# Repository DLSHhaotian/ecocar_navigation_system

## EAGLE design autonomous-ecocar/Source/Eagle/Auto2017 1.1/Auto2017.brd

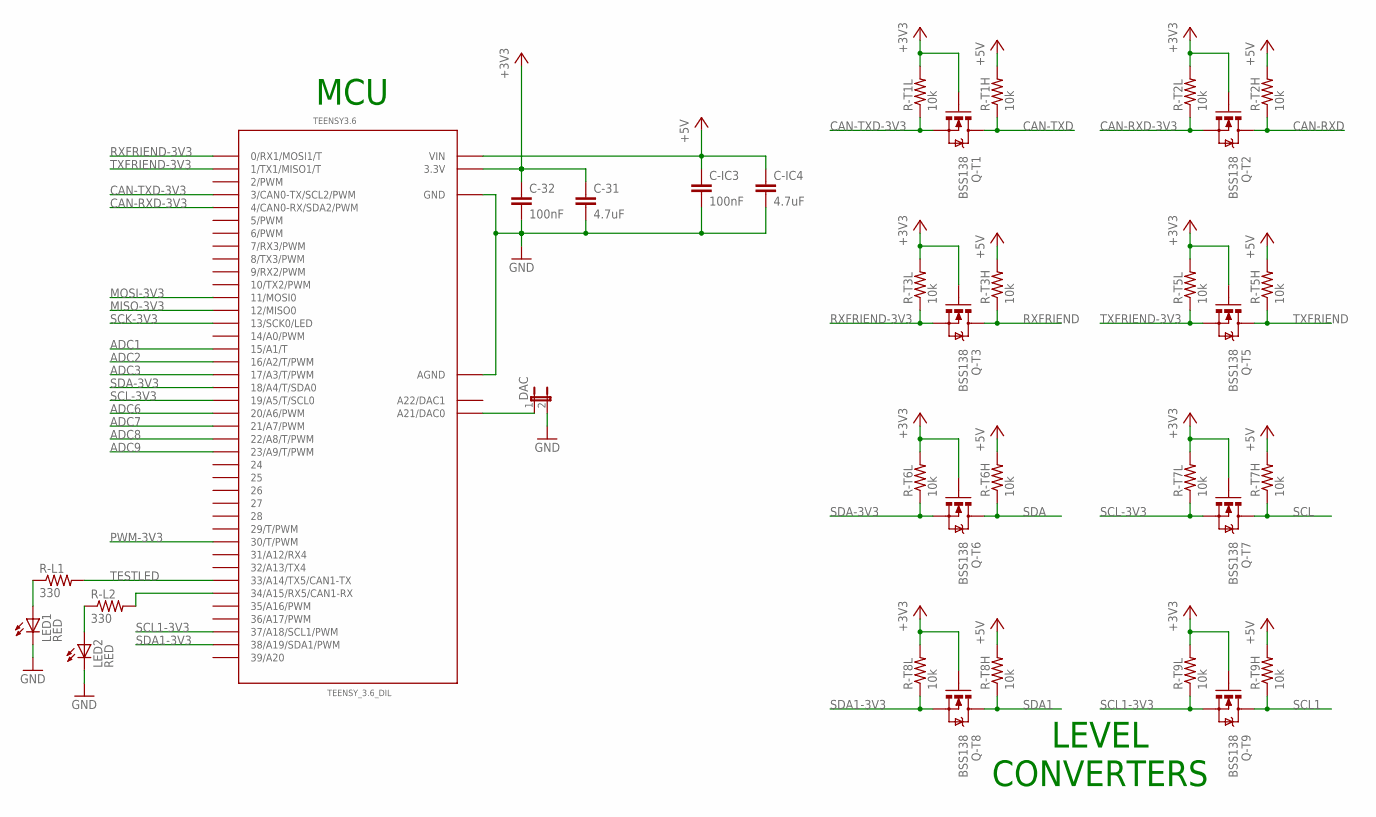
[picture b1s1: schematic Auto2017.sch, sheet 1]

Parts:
C-31: 4.7uF; 1210
C-32: 100nF; 0805
C-IC3: 100nF; 0805
C-IC4: 4.7uF; 1210
DAC: JUMPER-2PTH; 1X02
LED1, LED2: RED; LED-1206
Q-T1, Q-T2, Q-T3, Q-T5, Q-T6, Q-T7, Q-T8, Q-T9: BSS138; SOT23-3
R-L1, R-L2: 330; 0805
R-T1H, R-T1L, R-T2H, R-T2L, R-T3H, R-T3L, R-T5H, R-T5L, R-T6H, R-T6L, R-T7H, R-T7L, R-T8H, R-T8L, R-T9H, R-T9L: 10k; 0805
TEENSY3.6: TEENSY_3.6_DIL

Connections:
+3V3: C-31.1, C-32.1, Q-T1.1 (G), Q-T2.1 (G), Q-T3.1 (G), Q-T5.1 (G), Q-T6.1 (G), Q-T7.1 (G), Q-T8.1 (G), Q-T9.1 (G), R-T1L.2, R-T2L.2, R-T3L.2, R-T5L.2, R-T6L.2, R-T7L.2, R-T8L.2, R-T9L.2, TEENSY3.6.3.3V, TEENSY3.6.3.3V3 (3.3V); also elsewhere on the board
+5V: C-IC3.1, C-IC4.1, R-T1H.2, R-T2H.2, R-T3H.2, R-T5H.2, R-T6H.2, R-T7H.2, R-T8H.2, R-T9H.2, TEENSY3.6.VIN; also elsewhere on the board
ADC1: TEENSY3.6.15/A1 (15/A1/T); also elsewhere on the board
ADC2: TEENSY3.6.16/A2 (16/A2/T/PWM); also elsewhere on the board
ADC3: TEENSY3.6.17/A3 (17/A3/T/PWM); also elsewhere on the board
ADC6: TEENSY3.6.20/A6 (20/A6/PWM); also elsewhere on the board
ADC7: TEENSY3.6.21/A7 (21/A7/PWM); also elsewhere on the board
ADC8: TEENSY3.6.22/A8 (22/A8/T/PWM); also elsewhere on the board
ADC9: TEENSY3.6.23/A9 (23/A9/T/PWM); also elsewhere on the board
CAN-RXD: Q-T2.3 (D), R-T2H.1; also elsewhere on the board
CAN-RXD-3V3: Q-T2.2 (S), R-T2L.1, TEENSY3.6.4 (4/CAN0-RX/SDA2/PWM)
CAN-TXD: Q-T1.3 (D), R-T1H.1; also elsewhere on the board
CAN-TXD-3V3: Q-T1.2 (S), R-T1L.1, TEENSY3.6.3 (3/CAN0-TX/SCL2/PWM)
GND: C-31.2, C-32.2, C-IC3.2, C-IC4.2, DAC.2, LED1.C, LED2.C, TEENSY3.6.AGND, TEENSY3.6.GND, TEENSY3.6.GND1 (GND); also elsewhere on the board
MISO-3V3: TEENSY3.6.12 (12/MISO0); also elsewhere on the board
MOSI-3V3: TEENSY3.6.11 (11/MOSI0); also elsewhere on the board
unnamed: LED1.A, R-L1.1
unnamed: LED2.A, R-L2.1
unnamed: R-L2.2, TEENSY3.6.34/A15 (34/A15/RX5/CAN1-RX)
unnamed: DAC.1, TEENSY3.6.A21 (A21/DAC0)
PWM-3V3: TEENSY3.6.30 (30/T/PWM); also elsewhere on the board
RXFRIEND: Q-T3.3 (D), R-T3H.1; also elsewhere on the board
RXFRIEND-3V3: Q-T3.2 (S), R-T3L.1, TEENSY3.6.0 (0/RX1/MOSI1/T)
SCK-3V3: TEENSY3.6.13 (13/SCK0/LED); also elsewhere on the board
SCL: Q-T7.3 (D), R-T7H.1; also elsewhere on the board
SCL1: Q-T9.3 (D), R-T9H.1; also elsewhere on the board
SCL1-3V3: Q-T9.2 (S), R-T9L.1, TEENSY3.6.37/A18 (37/A18/SCL1/PWM)
SCL-3V3: Q-T7.2 (S), R-T7L.1, TEENSY3.6.19/A5 (19/A5/T/SCL0)
SDA: Q-T6.3 (D), R-T6H.1; also elsewhere on the board
SDA1: Q-T8.3 (D), R-T8H.1; also elsewhere on the board
SDA1-3V3: Q-T8.2 (S), R-T8L.1, TEENSY3.6.38/A19 (38/A19/SDA1/PWM)
SDA-3V3: Q-T6.2 (S), R-T6L.1, TEENSY3.6.18/A4 (18/A4/T/SDA0)
TESTLED: R-L1.2, TEENSY3.6.33/A14 (33/A14/TX5/CAN1-TX)
TXFRIEND: Q-T5.3 (D), R-T5H.1; also elsewhere on the board
TXFRIEND-3V3: Q-T5.2 (S), R-T5L.1, TEENSY3.6.1 (1/TX1/MISO1/T)

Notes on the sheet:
MCU
LEVEL CONVERTERS

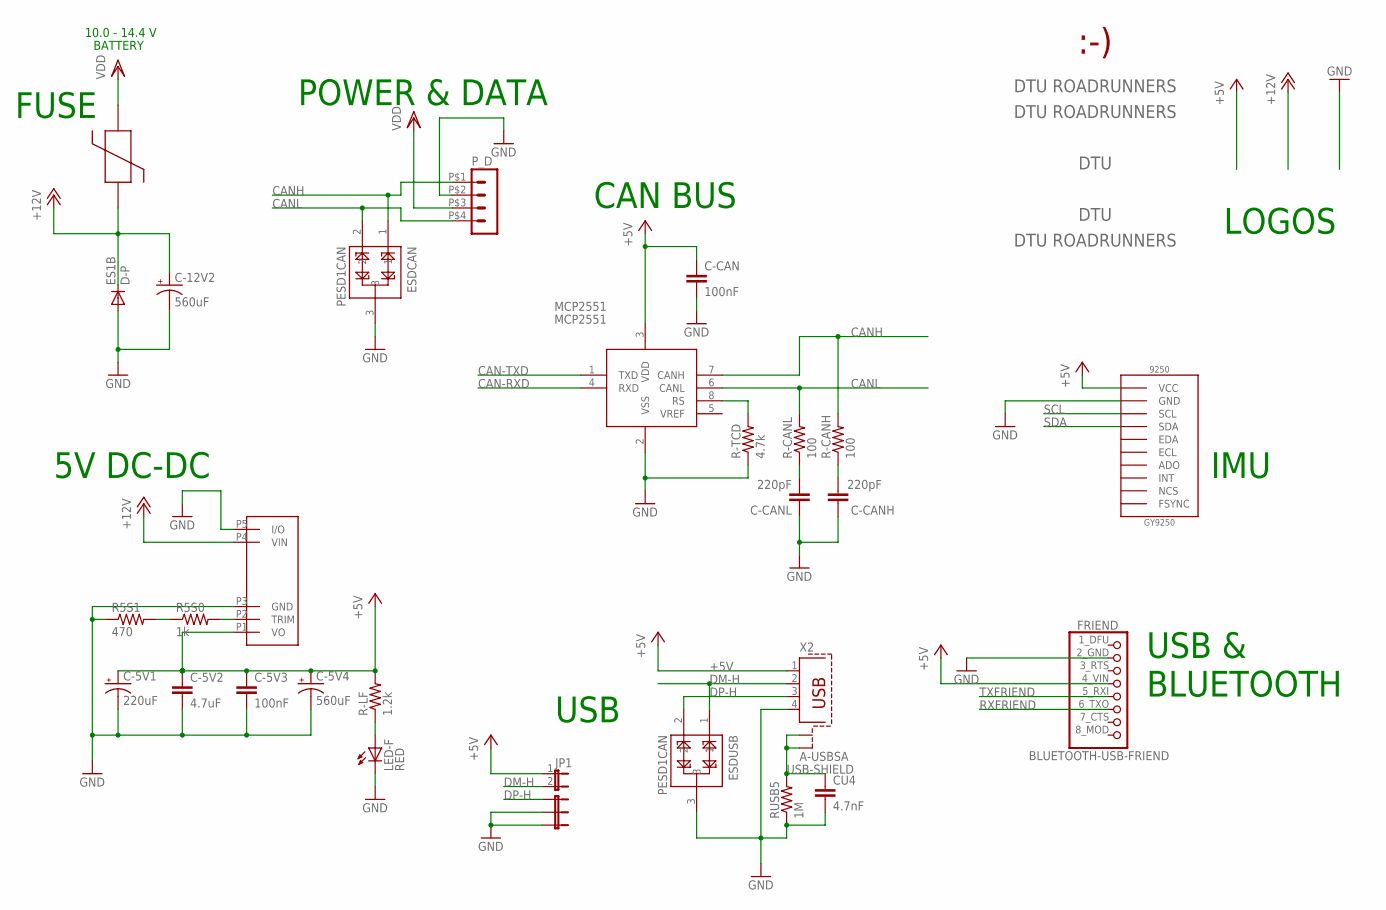
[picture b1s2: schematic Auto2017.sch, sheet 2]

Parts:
9250: GY9250
C-5V1: 220uF; PANASONIC_D
C-5V2: 4.7uF; 1210
C-5V3: 100nF; 0805
C-5V4, C-12V2: 560uF; PANASONIC_G
C-CAN: 100nF; 0805
C-CANH: 220pF; 0805
C-CANL: 220pF; 0805
CU4: 4.7nF; 0805
D-P: ES1B; SMA-DIODE
ESDCAN: PESD1CAN; SOT23-3
ESDUSB: PESD1CAN; SOT23-3
FRIEND: BLUETOOTH-USB-FRIEND; 1X08_ROUND_76
JP1: JUMPER-2PTH; 1X02
JP3: JUMPER-3PTH; 1X03
LED-F: RED; LED-1206
MAIN_FUSE: SMF_OMNI-BLOK_FUSE_BLOCK
MCP2551: MCP2551; SO-08M
P_D: HEADER_POS4_43045-0401; 43045-0400
R5S0: 1k; 0805
R5S1: 470; 0805
R-CANH: 100; 0805
R-CANL: 100; 0805
R-LF: 1.2k; 0805
R-TCD: 4.7k; 0805
RUSB5: 1M; 0805
U$1: AXA003A0XZ; SIP
U$3: DTUMEDIUM-9MM; DTU-MEDIUM-9MM
U$4, U$9: ROADRUNNERSFULL; ROADRUNNERS-FULL
U$5: ROADRUNNERSSMALL; ROADRUNNERS-SMALL
U$6: SMILEY
U$8: DTUSMALL; DTU-SMALL-5MM
X2: A-USBSA; USB-A

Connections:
+5V: 9250.P$VCC (VCC), C-5V1.+, C-5V2.1, C-5V3.1, C-5V4.+, C-CAN.1, FRIEND.4_VIN (4), JP1.1, MCP2551.3 (VDD), R-LF.2, U$1.P1 (VO), X2.1; also elsewhere on the board
+12V: C-12V2.+, D-P.C, MAIN_FUSE.PIN1, U$1.P4 (VIN)
CAN-RXD: MCP2551.4 (RXD); also elsewhere on the board
CAN-TXD: MCP2551.1 (TXD); also elsewhere on the board
CANH: ESDCAN.1, MCP2551.7 (CANH), P_D.P$1 (1), R-CANH.2
CANL: ESDCAN.2, MCP2551.6 (CANL), P_D.P$4 (4), R-CANL.2
DM-H: ESDUSB.1, JP1.2, X2.2
DP-H: ESDUSB.2, JP3.1, X2.3
GND: 9250.P$GND (GND), C-5V1.-, C-5V2.2, C-5V3.2, C-5V4.-, C-12V2.-, C-CAN.2, C-CANH.1, C-CANL.1, CU4.2, D-P.A, ESDCAN.3, ESDUSB.3, FRIEND.2_GND (2), JP3.2, JP3.3, LED-F.C, MCP2551.2 (VSS), P_D.P$2 (2), R5S1.1, R-TCD.1, RUSB5.1, U$1.P3 (GND), U$1.P5 (I/O), X2.4; also elsewhere on the board
unnamed: R5S0.1, R5S1.2
unnamed: R5S0.2, U$1.P2 (TRIM)
unnamed: LED-F.A, R-LF.1
unnamed: C-CANL.2, R-CANL.1
unnamed: C-CANH.2, R-CANH.1
RS: MCP2551.8 (RS), R-TCD.2
RXFRIEND: FRIEND.6_TXO (6); also elsewhere on the board
SCL: 9250.P$SCL (SCL); also elsewhere on the board
SDA: 9250.P$SDA (SDA); also elsewhere on the board
TXFRIEND: FRIEND.5_RXI (5); also elsewhere on the board
USB-SHIELD: CU4.1, RUSB5.2, X2.S1, X2.S2
VDD: MAIN_FUSE.PIN2, P_D.P$3 (3)

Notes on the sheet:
CAN BUS
5V DC-DC
BATTERY
10.0 - 14.4 V
POWER & DATA
FUSE
USB
USB & BLUETOOTH
IMU
LOGOS

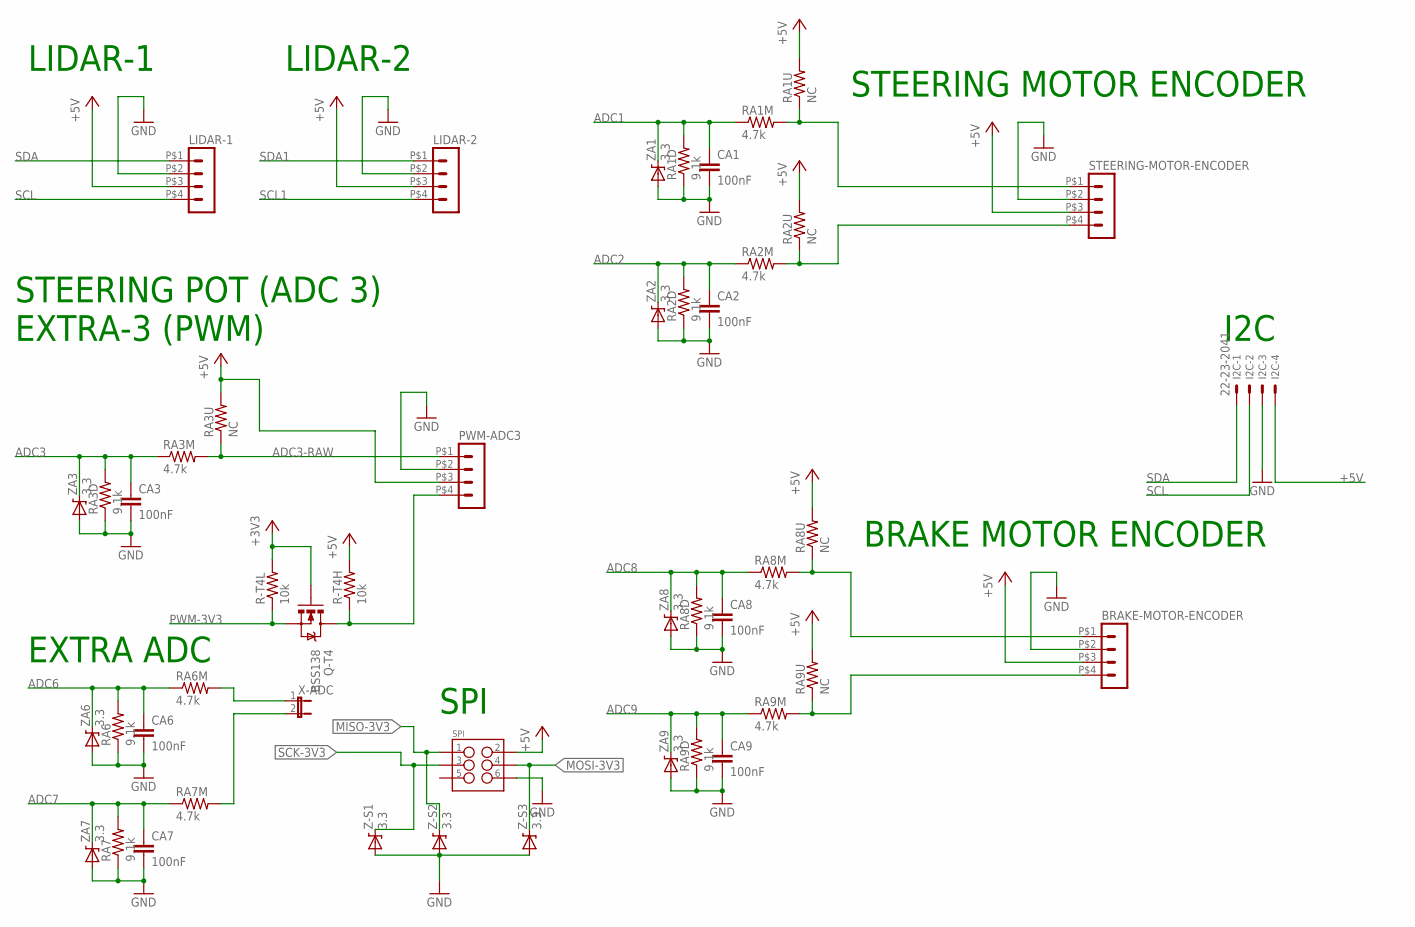
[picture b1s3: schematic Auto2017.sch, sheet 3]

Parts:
BRAKE-MOTOR-ENCODER: HEADER_POS4_43045-0401; 43045-0400
CA1, CA2, CA3, CA6, CA7, CA8, CA9: 100nF; 0805
I2C: 22-23-2041
LIDAR-1, LIDAR-2: HEADER_POS4_43045-0401; 43045-0400
PWM-ADC3: HEADER_POS4_43045-0401; 43045-0400
Q-T4: BSS138; SOT23-3
R-T4H, R-T4L: 10k; 0805
RA1D, RA2D, RA3D, RA6, RA7, RA8D, RA9D: 9.1k; 0805
RA1M, RA2M, RA3M, RA6M, RA7M, RA8M, RA9M: 4.7k; 0805
RA1U, RA2U, RA3U, RA8U, RA9U: NC; 0805
SPI: M03X2POGO_PINS; 2X3_POGO
STEERING-MOTOR-ENCODER: HEADER_POS4_43045-0401; 43045-0400
X-ADC: JUMPER-2PTH; 1X02
Z-S1, Z-S2, Z-S3: 3.3; SOD123
ZA1, ZA2, ZA3, ZA6, ZA7, ZA8, ZA9: 3.3; SOD123

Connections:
+3V3: Q-T4.1 (G), R-T4L.2; also elsewhere on the board
+5V: BRAKE-MOTOR-ENCODER.P$3 (3), I2C.4, LIDAR-1.P$3 (3), LIDAR-2.P$3 (3), PWM-ADC3.P$3 (3), R-T4H.2, RA1U.2, RA2U.2, RA3U.2, RA8U.2, RA9U.2, SPI.P$2 (2), STEERING-MOTOR-ENCODER.P$3 (3); also elsewhere on the board
ADC1: CA1.1, RA1D.2, RA1M.1, ZA1.C; also elsewhere on the board
ADC1-RAW: RA1M.2, RA1U.1, STEERING-MOTOR-ENCODER.P$1 (1)
ADC2: CA2.1, RA2D.2, RA2M.1, ZA2.C; also elsewhere on the board
ADC2-RAW: RA2M.2, RA2U.1, STEERING-MOTOR-ENCODER.P$4 (4)
ADC3: CA3.1, RA3D.2, RA3M.1, ZA3.C; also elsewhere on the board
ADC3-RAW: PWM-ADC3.P$1 (1), RA3M.2, RA3U.1
ADC6: CA6.1, RA6.2, RA6M.1, ZA6.C; also elsewhere on the board
ADC6-RAW: RA6M.2, X-ADC.1
ADC7: CA7.1, RA7.2, RA7M.1, ZA7.C; also elsewhere on the board
ADC7-RAW: RA7M.2, X-ADC.2
ADC8: CA8.1, RA8D.2, RA8M.1, ZA8.C; also elsewhere on the board
ADC8-RAW: BRAKE-MOTOR-ENCODER.P$1 (1), RA8M.2, RA8U.1
ADC9: CA9.1, RA9D.2, RA9M.1, ZA9.C; also elsewhere on the board
ADC9-RAW: BRAKE-MOTOR-ENCODER.P$4 (4), RA9M.2, RA9U.1
GND: BRAKE-MOTOR-ENCODER.P$2 (2), CA1.2, CA2.2, CA3.2, CA6.2, CA7.2, CA8.2, CA9.2, I2C.3, LIDAR-1.P$2 (2), LIDAR-2.P$2 (2), PWM-ADC3.P$2 (2), RA1D.1, RA2D.1, RA3D.1, RA6.1, RA7.1, RA8D.1, RA9D.1, SPI.P$6 (6), STEERING-MOTOR-ENCODER.P$2 (2), Z-S1.A, Z-S2.A, Z-S3.A, ZA1.A, ZA2.A, ZA3.A, ZA6.A, ZA7.A, ZA8.A, ZA9.A; also elsewhere on the board
MISO-3V3: SPI.P$1 (1), Z-S2.C; also elsewhere on the board
MOSI-3V3: SPI.P$4 (4), Z-S3.C; also elsewhere on the board
PWM-3V3: Q-T4.2 (S), R-T4L.1; also elsewhere on the board
PWM-5V: PWM-ADC3.P$4 (4), Q-T4.3 (D), R-T4H.1
SCK-3V3: SPI.P$3 (3), Z-S1.C; also elsewhere on the board
SCL: I2C.2, LIDAR-1.P$4 (4); also elsewhere on the board
SCL1: LIDAR-2.P$4 (4); also elsewhere on the board
SDA: I2C.1, LIDAR-1.P$1 (1); also elsewhere on the board
SDA1: LIDAR-2.P$1 (1); also elsewhere on the board

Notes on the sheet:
STEERING POT (ADC 3) EXTRA-3 (PWM)
SPI
LIDAR-1
LIDAR-2
STEERING MOTOR ENCODER
I2C
BRAKE MOTOR ENCODER
EXTRA ADC

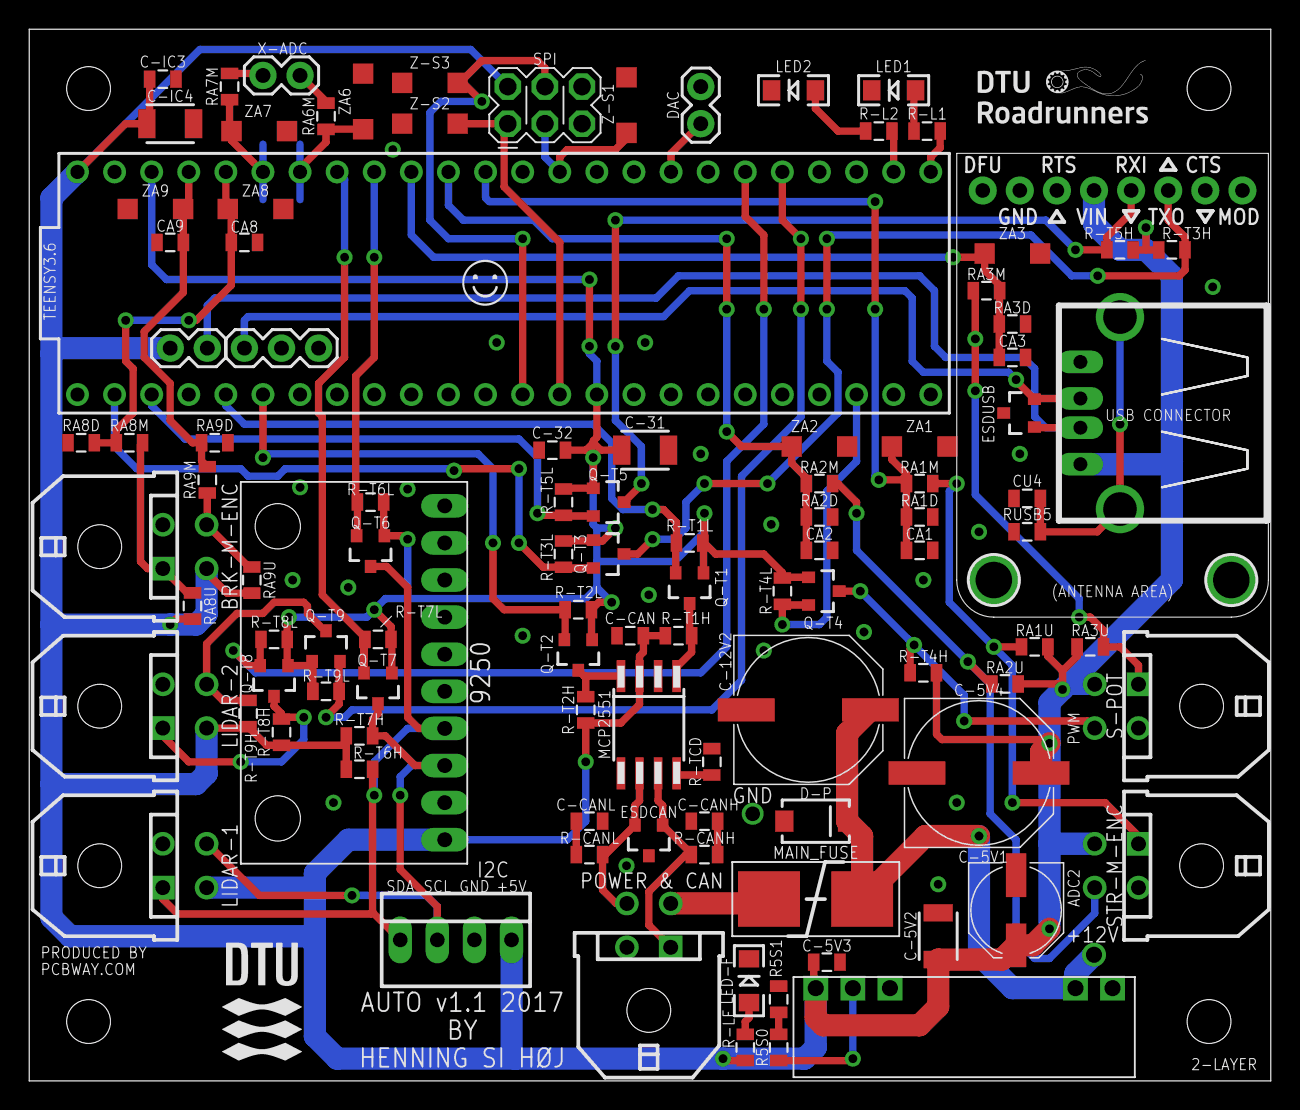
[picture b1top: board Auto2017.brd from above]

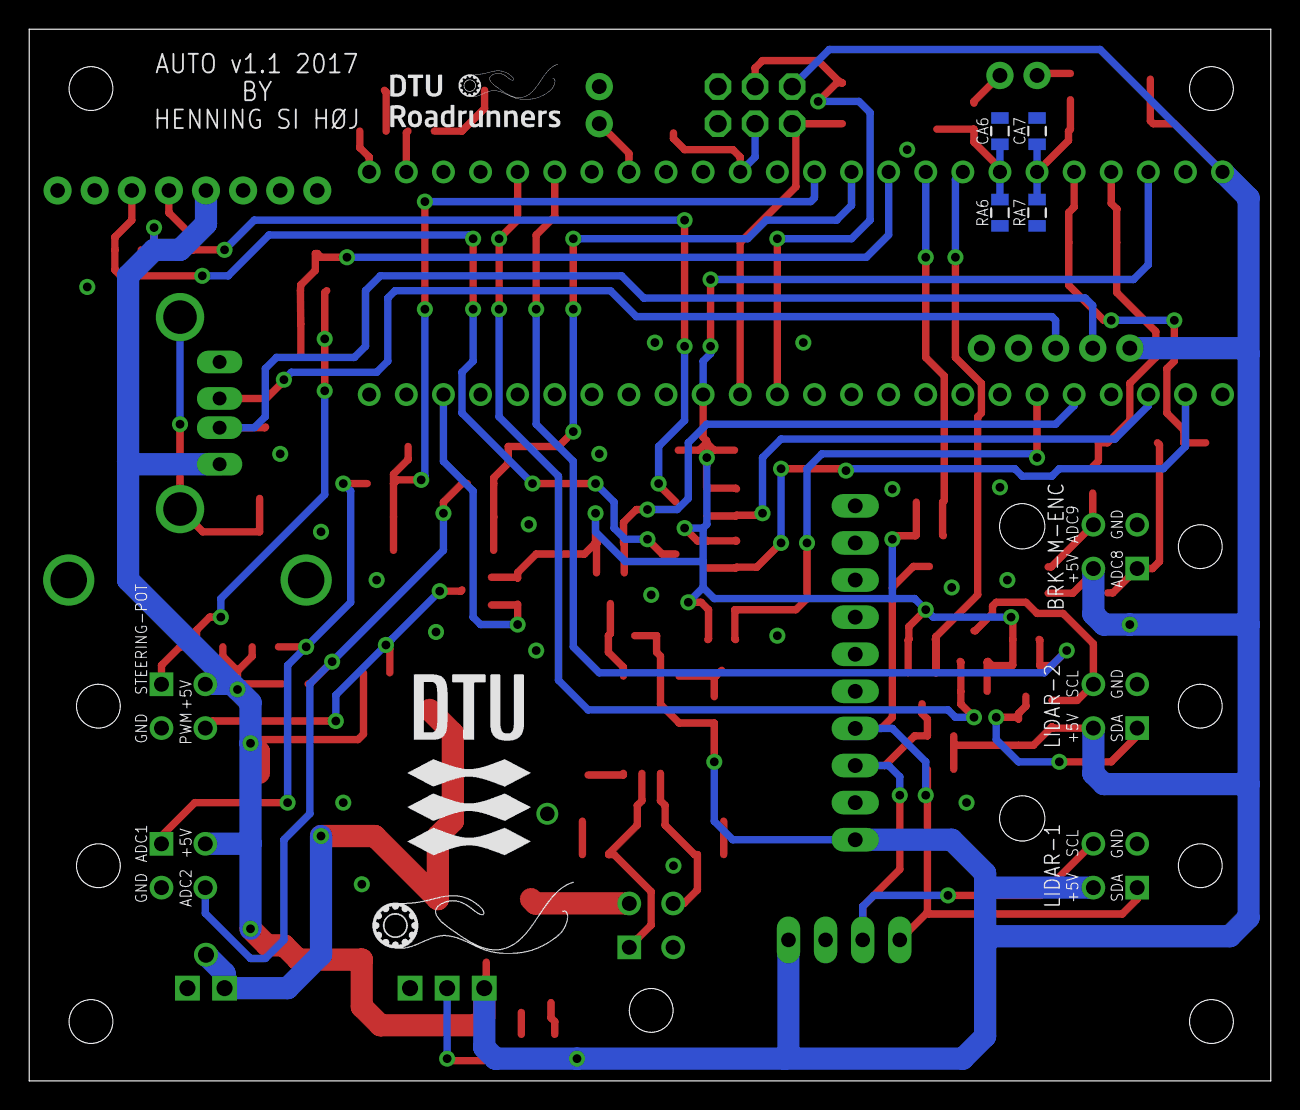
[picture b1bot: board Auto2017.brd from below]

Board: 2 copper layers, 85.0 x 72.0 mm, 116 parts (7 on the bottom side), 56 nets.

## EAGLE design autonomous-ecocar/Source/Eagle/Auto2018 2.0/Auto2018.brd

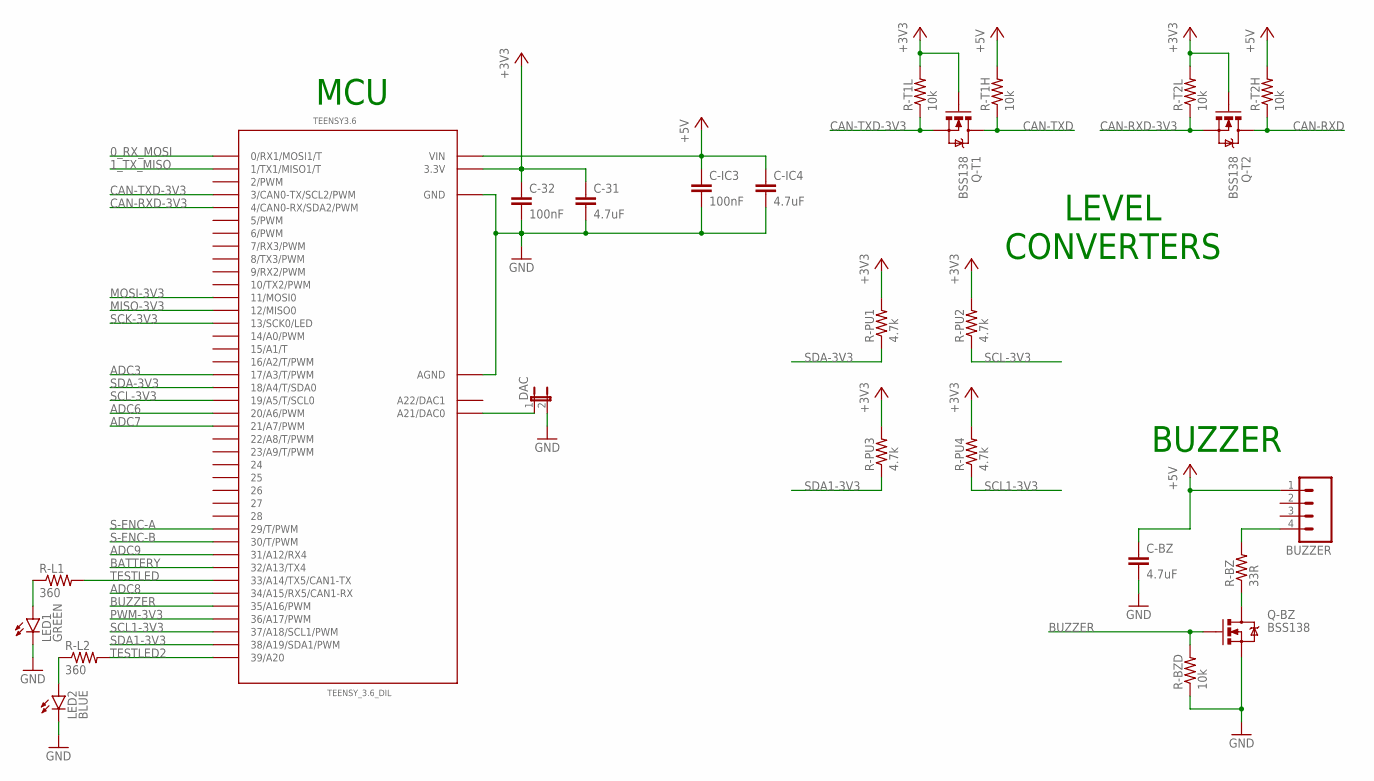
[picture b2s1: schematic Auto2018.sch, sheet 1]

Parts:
BUZZER: M04POLAR; MOLEX-1X4
C-31: 4.7uF; 1210
C-32: 100nF; 0805
C-BZ: 4.7uF; 1210
C-IC3: 100nF; 0805
C-IC4: 4.7uF; 1210
DAC: JUMPER-2PTH; 1X02
LED1: GREEN; LED-1206
LED2: BLUE; LED-1206
Q-BZ: BSS138; SOT23-3
Q-T1, Q-T2: BSS138; SOT23-3
R-BZ: 33R; 0805
R-BZD: 10k; 0805
R-L1, R-L2: 360; 0805
R-PU1, R-PU2, R-PU3, R-PU4: 4.7k; 0805
R-T1H, R-T1L, R-T2H, R-T2L: 10k; 0805
TEENSY3.6: TEENSY_3.6_DIL

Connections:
0_RX_MOSI: TEENSY3.6.0 (0/RX1/MOSI1/T); also elsewhere on the board
1_TX_MISO: TEENSY3.6.1 (1/TX1/MISO1/T); also elsewhere on the board
+3V3: C-31.1, C-32.1, Q-T1.1 (G), Q-T2.1 (G), R-PU1.2, R-PU2.2, R-PU3.2, R-PU4.2, R-T1L.2, R-T2L.2, TEENSY3.6.3.3V, TEENSY3.6.3.3V3 (3.3V); also elsewhere on the board
+5V: BUZZER.1, C-BZ.1, C-IC3.1, C-IC4.1, R-T1H.2, R-T2H.2, TEENSY3.6.VIN; also elsewhere on the board
ADC3: TEENSY3.6.17/A3 (17/A3/T/PWM); also elsewhere on the board
ADC6: TEENSY3.6.20/A6 (20/A6/PWM); also elsewhere on the board
ADC7: TEENSY3.6.21/A7 (21/A7/PWM); also elsewhere on the board
ADC8: TEENSY3.6.34/A15 (34/A15/RX5/CAN1-RX); also elsewhere on the board
ADC9: TEENSY3.6.31/A12 (31/A12/RX4); also elsewhere on the board
BATTERY: TEENSY3.6.32/A13 (32/A13/TX4); also elsewhere on the board
BUZZER: Q-BZ.1 (G), R-BZD.2, TEENSY3.6.35/A16 (35/A16/PWM)
CAN-RXD: Q-T2.3 (D), R-T2H.1; also elsewhere on the board
CAN-RXD-3V3: Q-T2.2 (S), R-T2L.1, TEENSY3.6.4 (4/CAN0-RX/SDA2/PWM)
CAN-TXD: Q-T1.3 (D), R-T1H.1; also elsewhere on the board
CAN-TXD-3V3: Q-T1.2 (S), R-T1L.1, TEENSY3.6.3 (3/CAN0-TX/SCL2/PWM)
GND: C-31.2, C-32.2, C-BZ.2, C-IC3.2, C-IC4.2, DAC.2, LED1.C, LED2.C, Q-BZ.2 (S), R-BZD.1, TEENSY3.6.AGND, TEENSY3.6.GND, TEENSY3.6.GND1 (GND); also elsewhere on the board
MISO-3V3: TEENSY3.6.12 (12/MISO0); also elsewhere on the board
MOSI-3V3: TEENSY3.6.11 (11/MOSI0); also elsewhere on the board
unnamed: LED1.A, R-L1.1
unnamed: LED2.A, R-L2.1
unnamed: DAC.1, TEENSY3.6.A21 (A21/DAC0)
unnamed: BUZZER.4, R-BZ.2
unnamed: Q-BZ.3 (D), R-BZ.1
PWM-3V3: TEENSY3.6.36/A17 (36/A17/PWM); also elsewhere on the board
S-ENC-A: TEENSY3.6.29 (29/T/PWM); also elsewhere on the board
S-ENC-B: TEENSY3.6.30 (30/T/PWM); also elsewhere on the board
SCK-3V3: TEENSY3.6.13 (13/SCK0/LED); also elsewhere on the board
SCL1-3V3: R-PU4.1, TEENSY3.6.37/A18 (37/A18/SCL1/PWM); also elsewhere on the board
SCL-3V3: R-PU2.1, TEENSY3.6.19/A5 (19/A5/T/SCL0); also elsewhere on the board
SDA1-3V3: R-PU3.1, TEENSY3.6.38/A19 (38/A19/SDA1/PWM); also elsewhere on the board
SDA-3V3: R-PU1.1, TEENSY3.6.18/A4 (18/A4/T/SDA0); also elsewhere on the board
TESTLED: R-L1.2, TEENSY3.6.33/A14 (33/A14/TX5/CAN1-TX)
TESTLED2: R-L2.2, TEENSY3.6.39/A20

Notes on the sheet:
MCU
LEVEL CONVERTERS
BUZZER

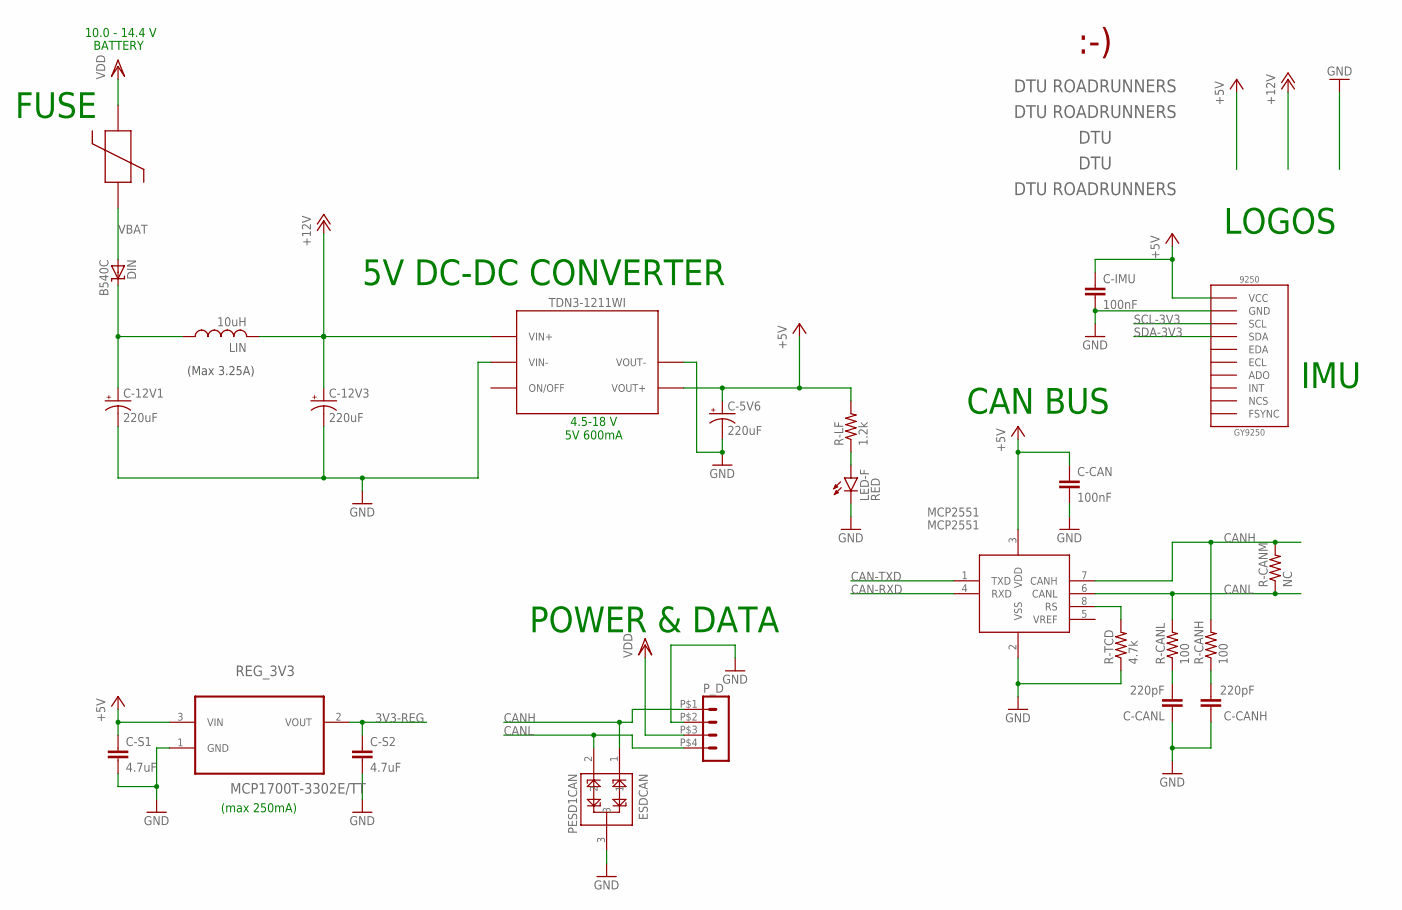
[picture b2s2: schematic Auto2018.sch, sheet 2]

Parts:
9250: GY9250
C-5V6, C-12V1, C-12V3: 220uF; PANASONIC_D
C-CAN: 100nF; 0805
C-CANH: 220pF; 0805
C-CANL: 220pF; 0805
C-IMU: 100nF; 0805
C-S1, C-S2: 4.7uF; 1210
DIN: B540C; SMC
ESDCAN: PESD1CAN; SOT23-3
LED-F: RED; LED-1206
LIN: 10uH; WE-LHMI_SMD_POWER_INDUCTOR
MAIN_FUSE: SMF_OMNI-BLOK_FUSE_BLOCK
MCP2551: MCP2551; SO-08M
P_D: HEADER_POS4_43045-0401; 43045-0400
R-CANH: 100; 0805
R-CANL: 100; 0805
R-CANM: NC; 0805
R-LF: 1.2k; 0805
R-TCD: 4.7k; 0805
REG_3V3: MCP1700T-3302E/TT; SOT95P237X112-3N
TDN3-1211WI: TDN3WI; TDC3WI
U$3: DTUMEDIUM-9MM; DTU-MEDIUM-9MM
U$4, U$9: ROADRUNNERSFULL; ROADRUNNERS-FULL
U$5: ROADRUNNERSSMALL; ROADRUNNERS-SMALL
U$6: SMILEY
U$8: DTUSMALL; DTU-SMALL-5MM

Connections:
3V3-REG: C-S2.1, REG_3V3.2 (VOUT); also elsewhere on the board
+5V: 9250.P$VCC (VCC), C-5V6.+, C-CAN.1, C-IMU.1, C-S1.1, MCP2551.3 (VDD), R-LF.2, REG_3V3.3 (VIN), TDN3-1211WI.VOUT+; also elsewhere on the board
+12V: C-12V3.+, LIN.P$2 (2), TDN3-1211WI.VIN+
CAN-RXD: MCP2551.4 (RXD); also elsewhere on the board
CAN-TXD: MCP2551.1 (TXD); also elsewhere on the board
CANH: ESDCAN.1, MCP2551.7 (CANH), P_D.P$1 (1), R-CANH.2, R-CANM.2
CANL: ESDCAN.2, MCP2551.6 (CANL), P_D.P$4 (4), R-CANL.2, R-CANM.1
GND: 9250.P$GND (GND), C-5V6.-, C-12V1.-, C-12V3.-, C-CAN.2, C-CANH.1, C-CANL.1, C-IMU.2, C-S1.2, C-S2.2, ESDCAN.3, LED-F.C, MCP2551.2 (VSS), P_D.P$2 (2), R-TCD.1, REG_3V3.1 (GND), TDN3-1211WI.VIN-, TDN3-1211WI.VOUT-; also elsewhere on the board
unnamed: C-12V1.+, DIN.C, LIN.P$1 (1)
unnamed: LED-F.A, R-LF.1
unnamed: C-CANL.2, R-CANL.1
unnamed: C-CANH.2, R-CANH.1
RS: MCP2551.8 (RS), R-TCD.2
SCL-3V3: 9250.P$SCL (SCL); also elsewhere on the board
SDA-3V3: 9250.P$SDA (SDA); also elsewhere on the board
VBAT: DIN.A, MAIN_FUSE.PIN1; also elsewhere on the board
VDD: MAIN_FUSE.PIN2, P_D.P$3 (3)

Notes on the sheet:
CAN BUS
BATTERY
10.0 - 14.4 V
POWER & DATA
FUSE
IMU
LOGOS
5V DC-DC CONVERTER
(Max 3.25A)
4.5-18 V 5V 600mA
(max 250mA)

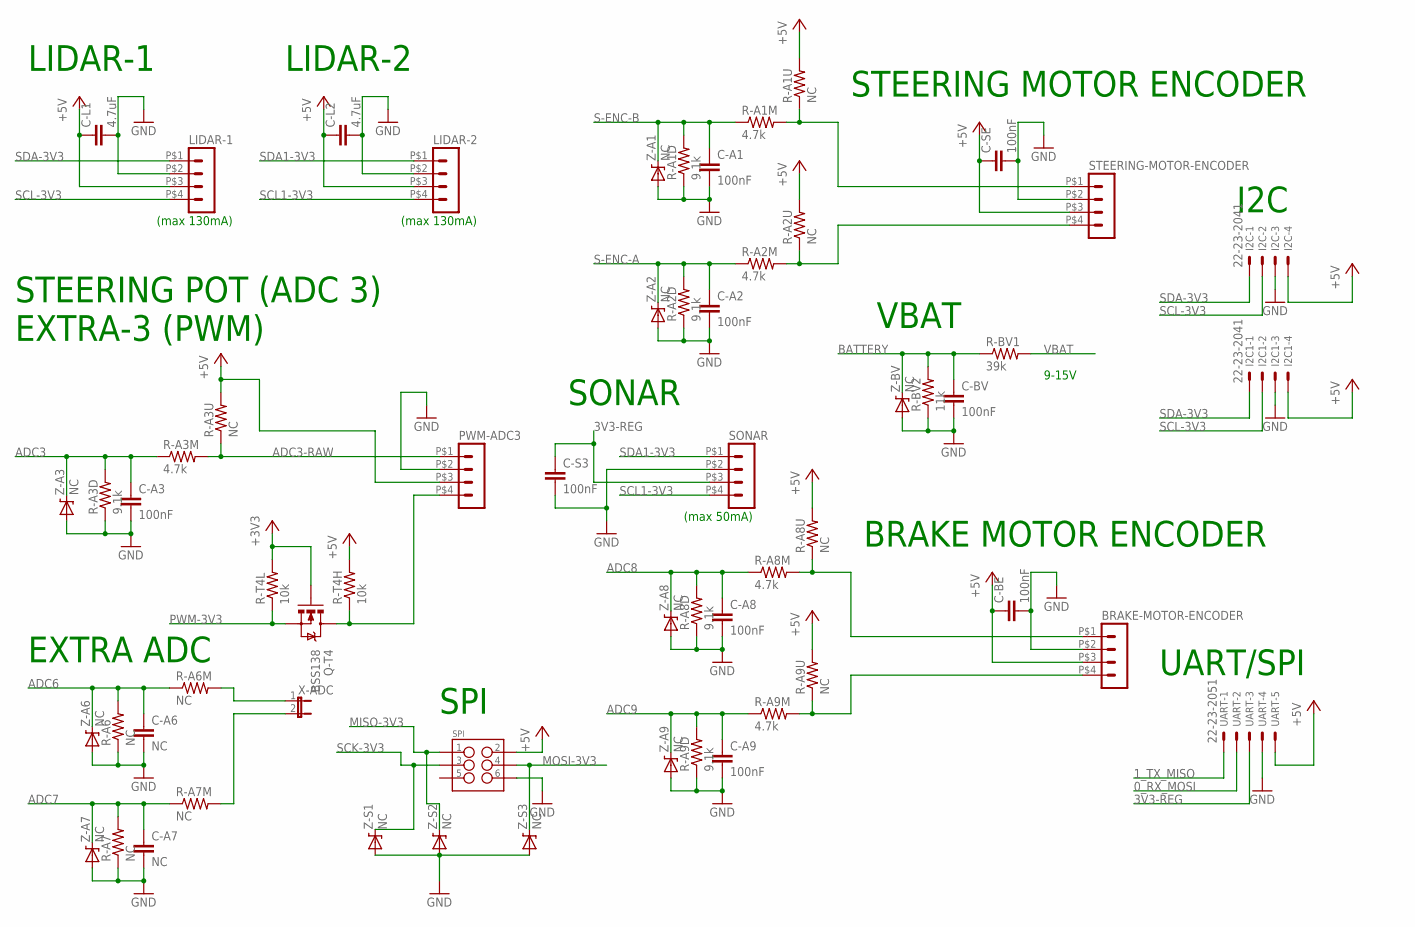
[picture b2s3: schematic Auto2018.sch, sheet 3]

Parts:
BRAKE-MOTOR-ENCODER: HEADER_POS4_43045-0401; 43045-0400
C-A1, C-A2, C-A3, C-A8, C-A9: 100nF; 0805
C-A6, C-A7: NC; 0805
C-BE: 100nF; 0805
C-BV: 100nF; 0805
C-L1, C-L2: 4.7uF; 1210
C-S3: 100nF; 0805
C-SE: 100nF; 0805
I2C, I2C1: 22-23-2041
LIDAR-1, LIDAR-2: HEADER_POS4_43045-0401; 43045-0400
PWM-ADC3: HEADER_POS4_43045-0401; 43045-0400
Q-T4: BSS138; SOT23-3
R-A1D, R-A2D, R-A3D, R-A8D, R-A9D: 9.1k; 0805
R-A1M, R-A2M, R-A3M, R-A8M, R-A9M: 4.7k; 0805
R-A1U, R-A2U, R-A3U, R-A6, R-A6M, R-A7, R-A7M, R-A8U, R-A9U: NC; 0805
R-BV1: 39k; 0805
R-BV2: 11k; 0805
R-T4H, R-T4L: 10k; 0805
SONAR: HEADER_POS4_43045-0401; 43045-0400
SPI: M03X2POGO_PINS; 2X3_POGO
STEERING-MOTOR-ENCODER: HEADER_POS4_43045-0401; 43045-0400
UART: 22-23-2051
X-ADC: JUMPER-2PTH; 1X02
Z-A1, Z-A2, Z-A3, Z-A6, Z-A7, Z-A8, Z-A9: NC; SOD123@1
Z-BV: NC; SOD123@1
Z-S1, Z-S2, Z-S3: NC; SOD123@1

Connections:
0_RX_MOSI: UART.2; also elsewhere on the board
1_TX_MISO: UART.1; also elsewhere on the board
3V3-REG: C-S3.1, SONAR.P$3 (3), UART.3; also elsewhere on the board
+3V3: Q-T4.1 (G), R-T4L.2; also elsewhere on the board
+5V: BRAKE-MOTOR-ENCODER.P$3 (3), C-BE.1, C-L1.1, C-L2.1, C-SE.1, I2C.4, I2C1.4, LIDAR-1.P$3 (3), LIDAR-2.P$3 (3), PWM-ADC3.P$3 (3), R-A1U.2, R-A2U.2, R-A3U.2, R-A8U.2, R-A9U.2, R-T4H.2, SPI.P$2 (2), STEERING-MOTOR-ENCODER.P$3 (3), UART.5; also elsewhere on the board
ADC3: C-A3.1, R-A3D.2, R-A3M.1, Z-A3.C; also elsewhere on the board
ADC3-RAW: PWM-ADC3.P$1 (1), R-A3M.2, R-A3U.1
ADC6: C-A6.1, R-A6.2, R-A6M.1, Z-A6.C; also elsewhere on the board
ADC6-RAW: R-A6M.2, X-ADC.1
ADC7: C-A7.1, R-A7.2, R-A7M.1, Z-A7.C; also elsewhere on the board
ADC7-RAW: R-A7M.2, X-ADC.2
ADC8: C-A8.1, R-A8D.2, R-A8M.1, Z-A8.C; also elsewhere on the board
ADC8-RAW: BRAKE-MOTOR-ENCODER.P$1 (1), R-A8M.2, R-A8U.1
ADC9: C-A9.1, R-A9D.2, R-A9M.1, Z-A9.C; also elsewhere on the board
ADC9-RAW: BRAKE-MOTOR-ENCODER.P$4 (4), R-A9M.2, R-A9U.1
BATTERY: C-BV.1, R-BV1.1, R-BV2.2, Z-BV.C; also elsewhere on the board
GND: BRAKE-MOTOR-ENCODER.P$2 (2), C-A1.2, C-A2.2, C-A3.2, C-A6.2, C-A7.2, C-A8.2, C-A9.2, C-BE.2, C-BV.2, C-L1.2, C-L2.2, C-S3.2, C-SE.2, I2C.3, I2C1.3, LIDAR-1.P$2 (2), LIDAR-2.P$2 (2), PWM-ADC3.P$2 (2), R-A1D.1, R-A2D.1, R-A3D.1, R-A6.1, R-A7.1, R-A8D.1, R-A9D.1, R-BV2.1, SONAR.P$2 (2), SPI.P$6 (6), STEERING-MOTOR-ENCODER.P$2 (2), UART.4, Z-A1.A, Z-A2.A, Z-A3.A, Z-A6.A, Z-A7.A, Z-A8.A, Z-A9.A, Z-BV.A, Z-S1.A, Z-S2.A, Z-S3.A; also elsewhere on the board
MISO-3V3: SPI.P$1 (1), Z-S2.C; also elsewhere on the board
MOSI-3V3: SPI.P$4 (4), Z-S3.C; also elsewhere on the board
PWM-3V3: Q-T4.2 (S), R-T4L.1; also elsewhere on the board
PWM-5V: PWM-ADC3.P$4 (4), Q-T4.3 (D), R-T4H.1
S-ENC-A: C-A2.1, R-A2D.2, R-A2M.1, Z-A2.C; also elsewhere on the board
S-ENC-A-RAW: R-A2M.2, R-A2U.1, STEERING-MOTOR-ENCODER.P$4 (4)
S-ENC-B: C-A1.1, R-A1D.2, R-A1M.1, Z-A1.C; also elsewhere on the board
S-ENC-B-RAW: R-A1M.2, R-A1U.1, STEERING-MOTOR-ENCODER.P$1 (1)
SCK-3V3: SPI.P$3 (3), Z-S1.C; also elsewhere on the board
SCL1-3V3: LIDAR-2.P$4 (4), SONAR.P$4 (4); also elsewhere on the board
SCL-3V3: I2C.2, I2C1.2, LIDAR-1.P$4 (4); also elsewhere on the board
SDA1-3V3: LIDAR-2.P$1 (1), SONAR.P$1 (1); also elsewhere on the board
SDA-3V3: I2C.1, I2C1.1, LIDAR-1.P$1 (1); also elsewhere on the board
VBAT: R-BV1.2; also elsewhere on the board

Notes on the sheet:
STEERING POT (ADC 3) EXTRA-3 (PWM)
SPI
LIDAR-1
LIDAR-2
STEERING MOTOR ENCODER
I2C
BRAKE MOTOR ENCODER
EXTRA ADC
(max 130mA)
VBAT
SONAR
(max 50mA)
UART/SPI
9-15V

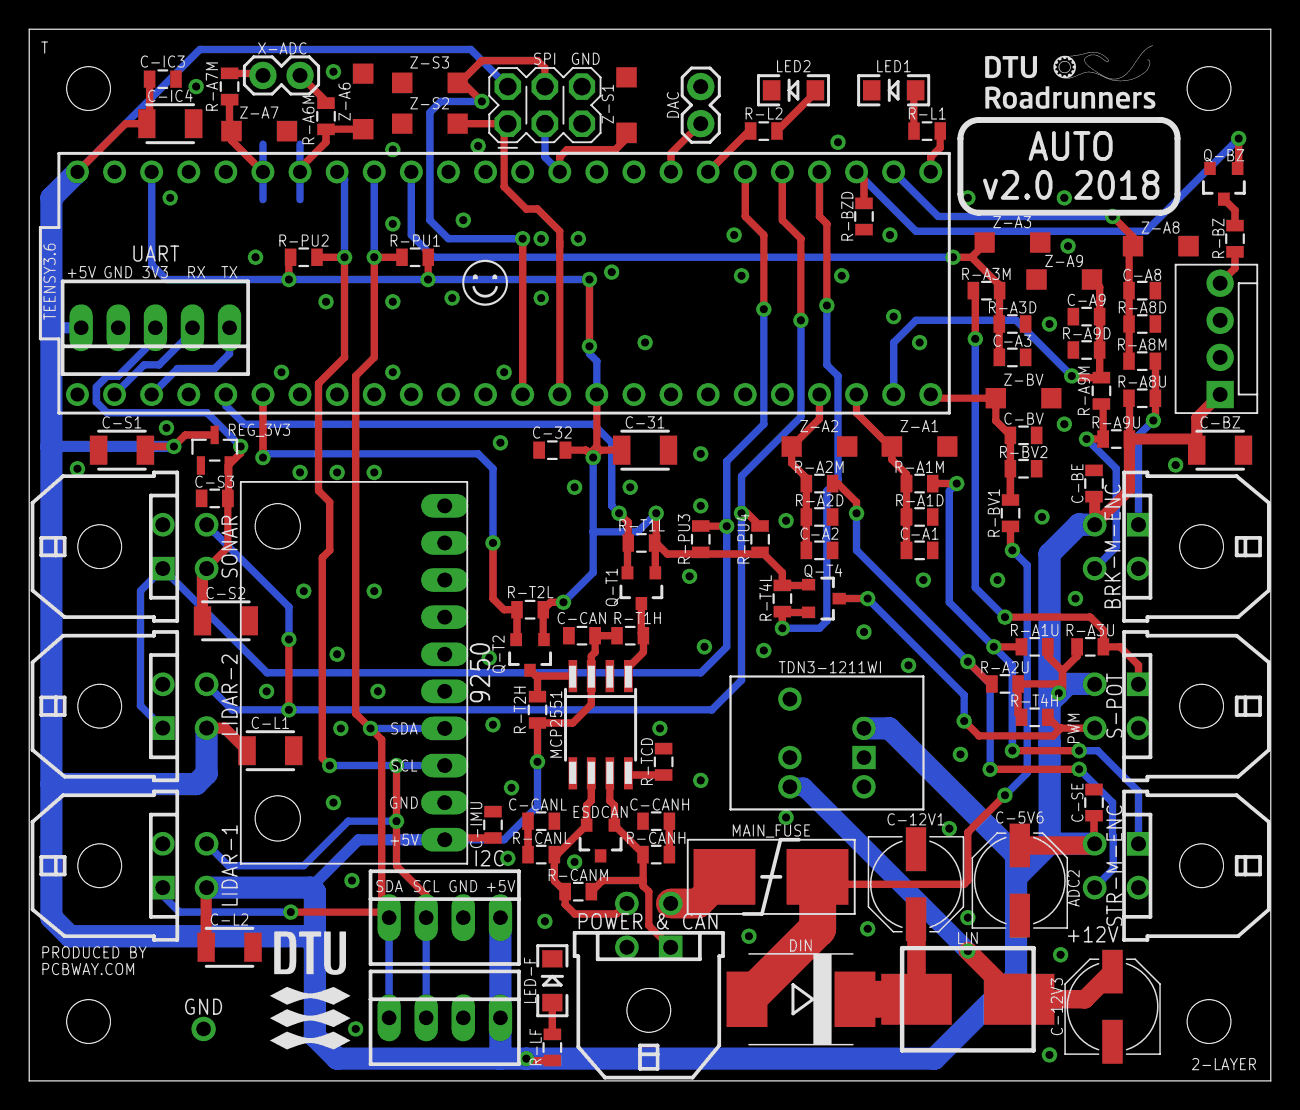
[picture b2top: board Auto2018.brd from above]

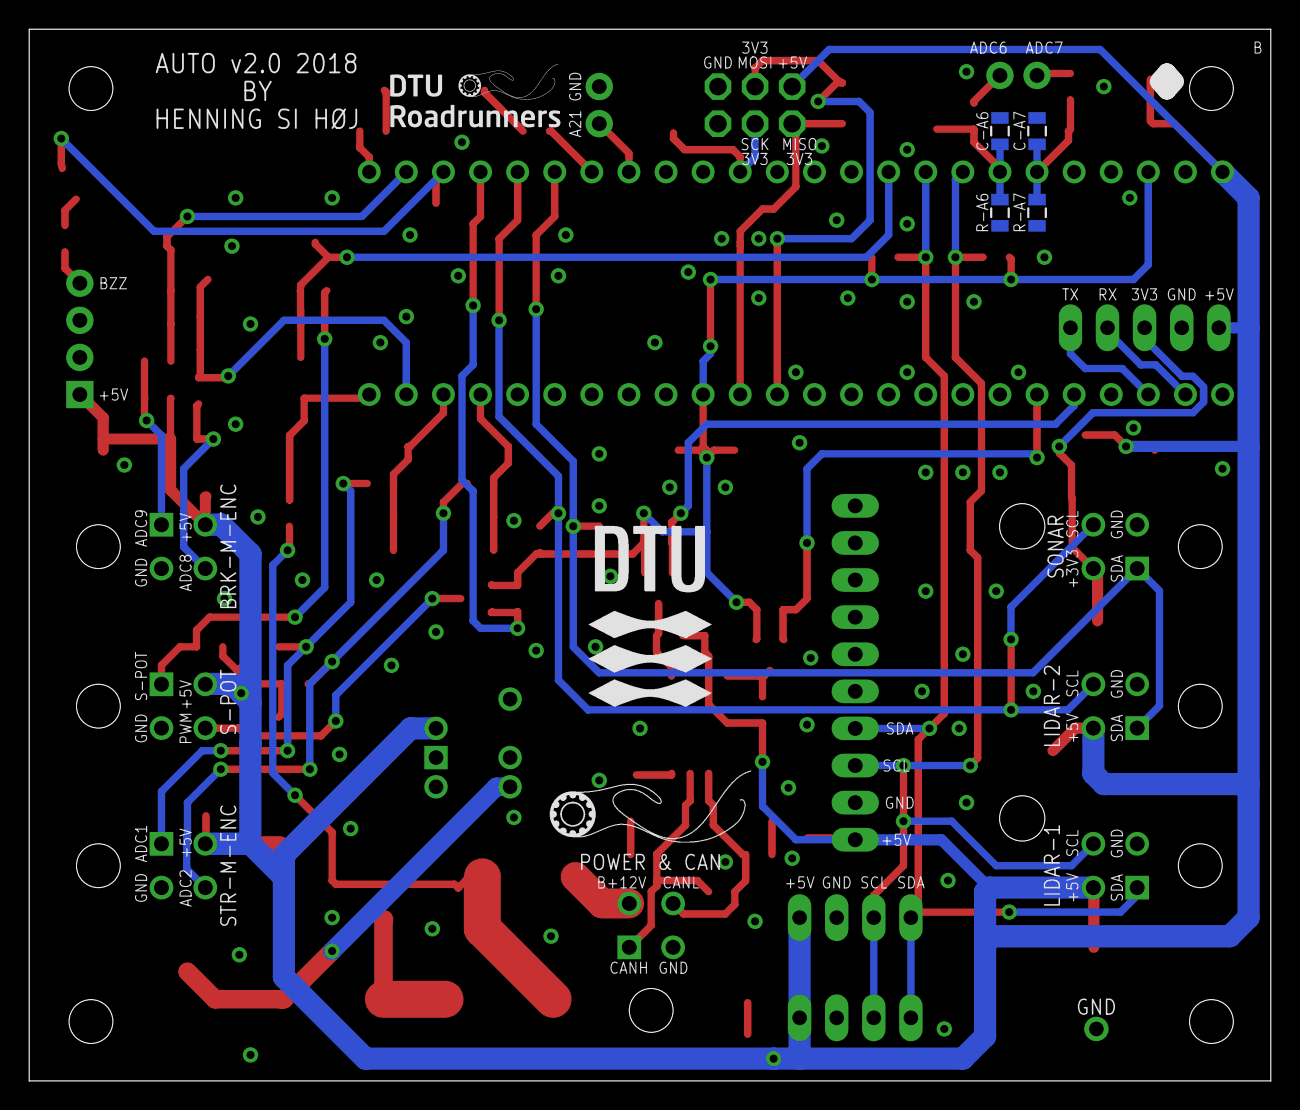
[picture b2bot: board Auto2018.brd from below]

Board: 2 copper layers, 85.0 x 72.0 mm, 114 parts (7 on the bottom side), 52 nets.

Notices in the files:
parts and their libraries:
SparkFun-Resistors: Licensing: CC v3.0 Share-Alike You are welcome to use this library for commercial purposes.
SparkFun-Retired: Licensing:Creative Commons ShareAlike 4.0 International - https://creativecommons.org/licenses/by-sa/4.0
Wurth_Elektronik_Passive_rev18f: Copyright: Würth Elektronik
